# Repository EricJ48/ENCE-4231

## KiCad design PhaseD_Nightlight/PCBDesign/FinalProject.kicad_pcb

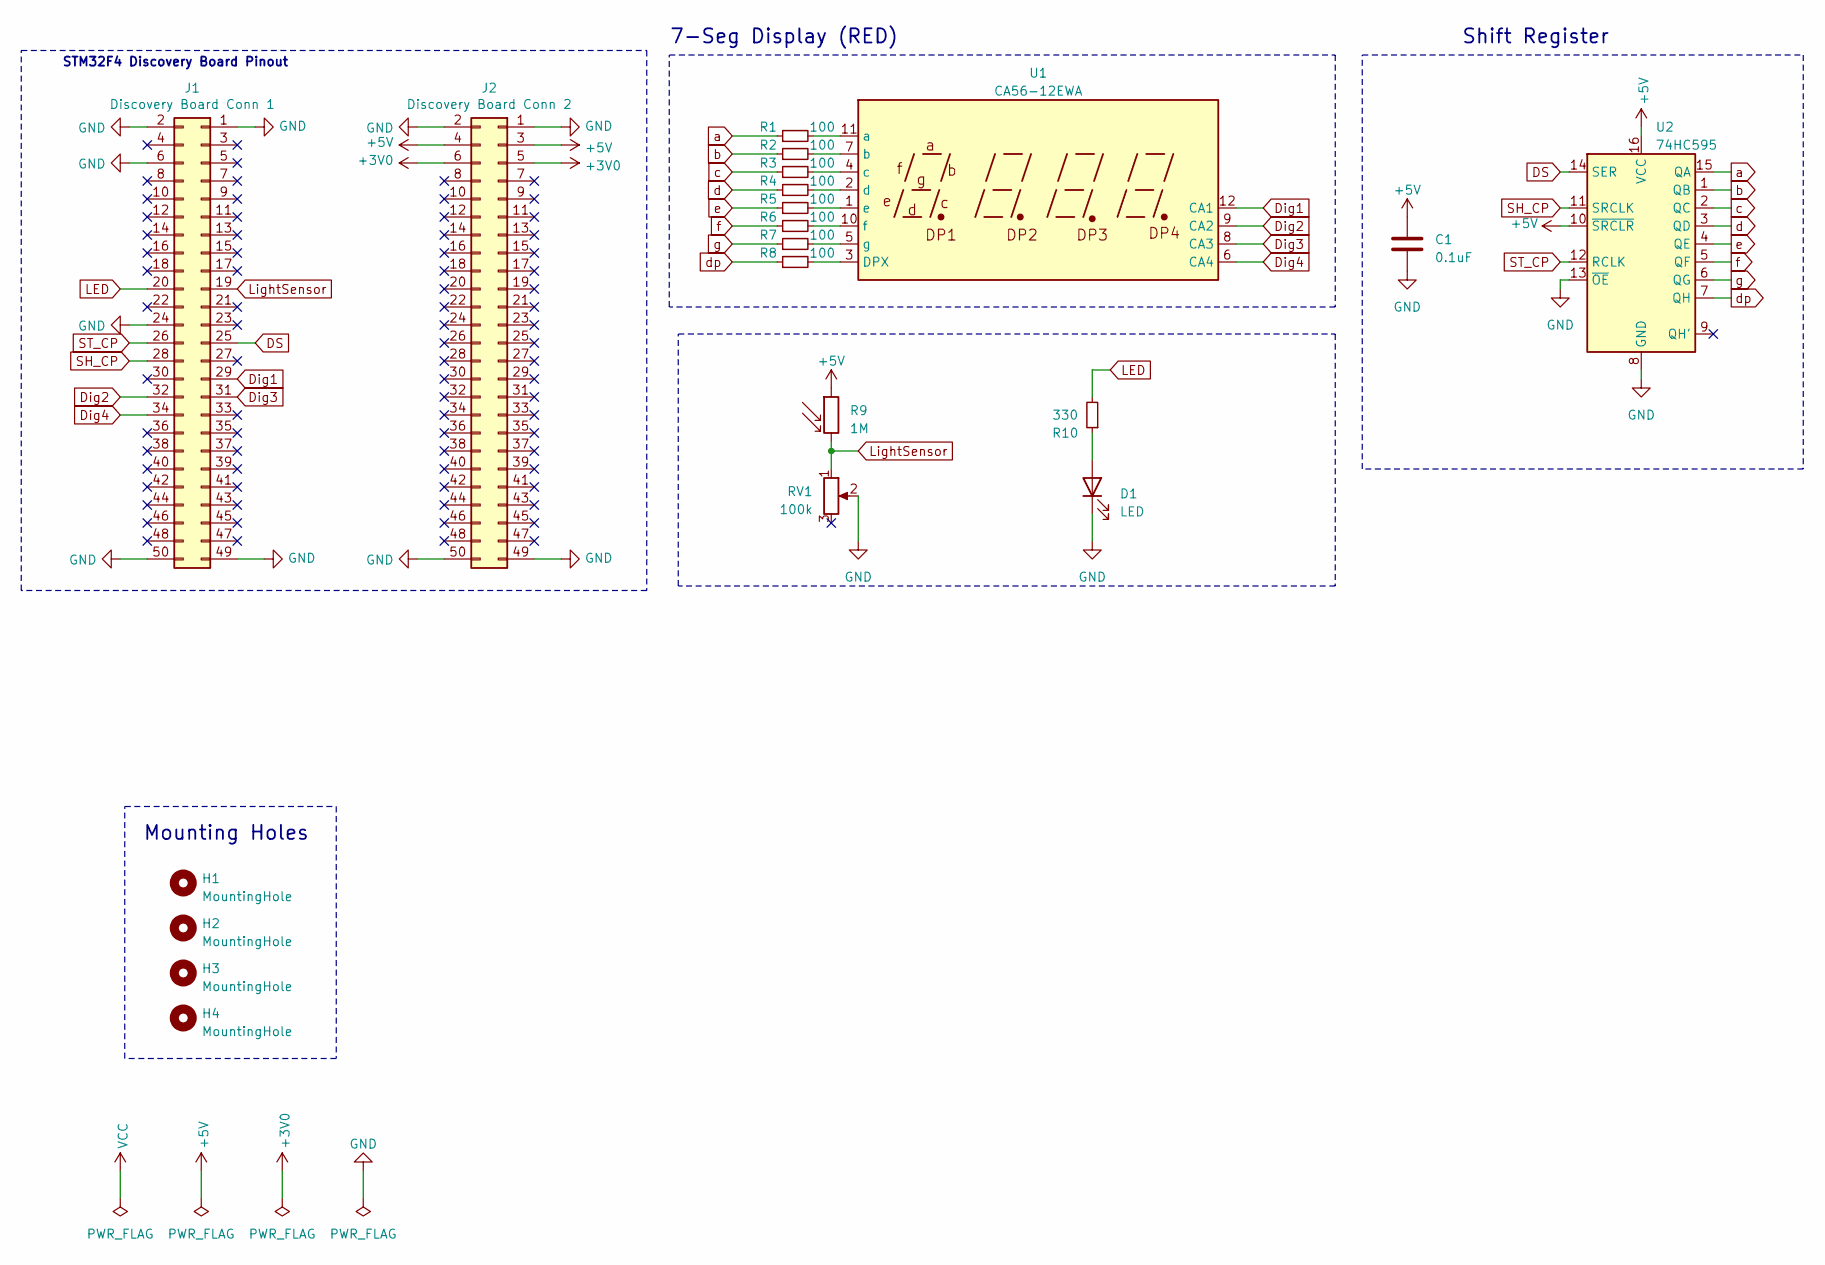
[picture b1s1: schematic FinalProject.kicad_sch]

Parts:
C1: 0.1uF; C_0603_1608Metric
D1: LED; LED_0805_2012Metric
H1, H2, H3, H4: MountingHole; MountingHole_3.2mm_M3_Pad
J1: Discovery Board Conn 1; PinSocket_2x25_P2.54mm_Vertical
J2: Discovery Board Conn 2; PinSocket_2x25_P2.54mm_Vertical
R1, R2, R3, R4, R5, R6, R7, R8: 100; R_0805_2012Metric
R9: 1M; R_Axial_DIN0204_L3.6mm_D1.6mm_P1.90mm_Vertical
R10: 330; R_0805_2012Metric
RV1: 100k; Potentiometer_ACP_CA9-VSMD_Vertical
U1: CA56-12EWA
U2: 74HC595; TSSOP-16_4.4x5mm_P0.65mm

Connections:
+3V0: J2.5, J2.6
+5V: C1.1, J2.3, J2.4, R9.1, U2.10 (~SRCLR), U2.16 (VCC)
DS: J1.25, U2.14 (SER)
Dig1: J1.29, U1.12 (CA1)
Dig2: J1.32, U1.9 (CA2)
Dig3: J1.31, U1.8 (CA3)
Dig4: J1.34, U1.6 (CA4)
GND: C1.2, D1.1 (K), J1.1, J1.2, J1.6, J1.24, J1.49, J1.50, J2.1, J2.2, J2.49, J2.50, RV1.2, U2.8 (GND), U2.13 (~OE)
LED: J1.20, R10.2
LightSensor: J1.19, R9.2, RV1.1
unnamed: D1.2 (A), R10.1
unnamed: R8.2, U1.3 (DPX)
unnamed: R1.2, U1.11 (a)
unnamed: R2.2, U1.7 (b)
unnamed: R3.2, U1.4 (c)
unnamed: R4.2, U1.2 (d)
unnamed: R5.2, U1.1 (e)
unnamed: R6.2, U1.10 (f)
unnamed: R7.2, U1.5 (g)
SH_CP: J1.28, U2.11 (SRCLK)
ST_CP: J1.26, U2.12 (RCLK)
a: R1.1, U2.15 (QA)
b: R2.1, U2.1 (QB)
c: R3.1, U2.2 (QC)
d: R4.1, U2.3 (QD)
dp: R8.1, U2.7 (QH)
e: R5.1, U2.4 (QE)
f: R6.1, U2.5 (QF)
g: R7.1, U2.6 (QG)

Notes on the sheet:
Mounting Holes
STM32F4 Discovery Board Pinout
7-Seg Display (RED)
Shift Register

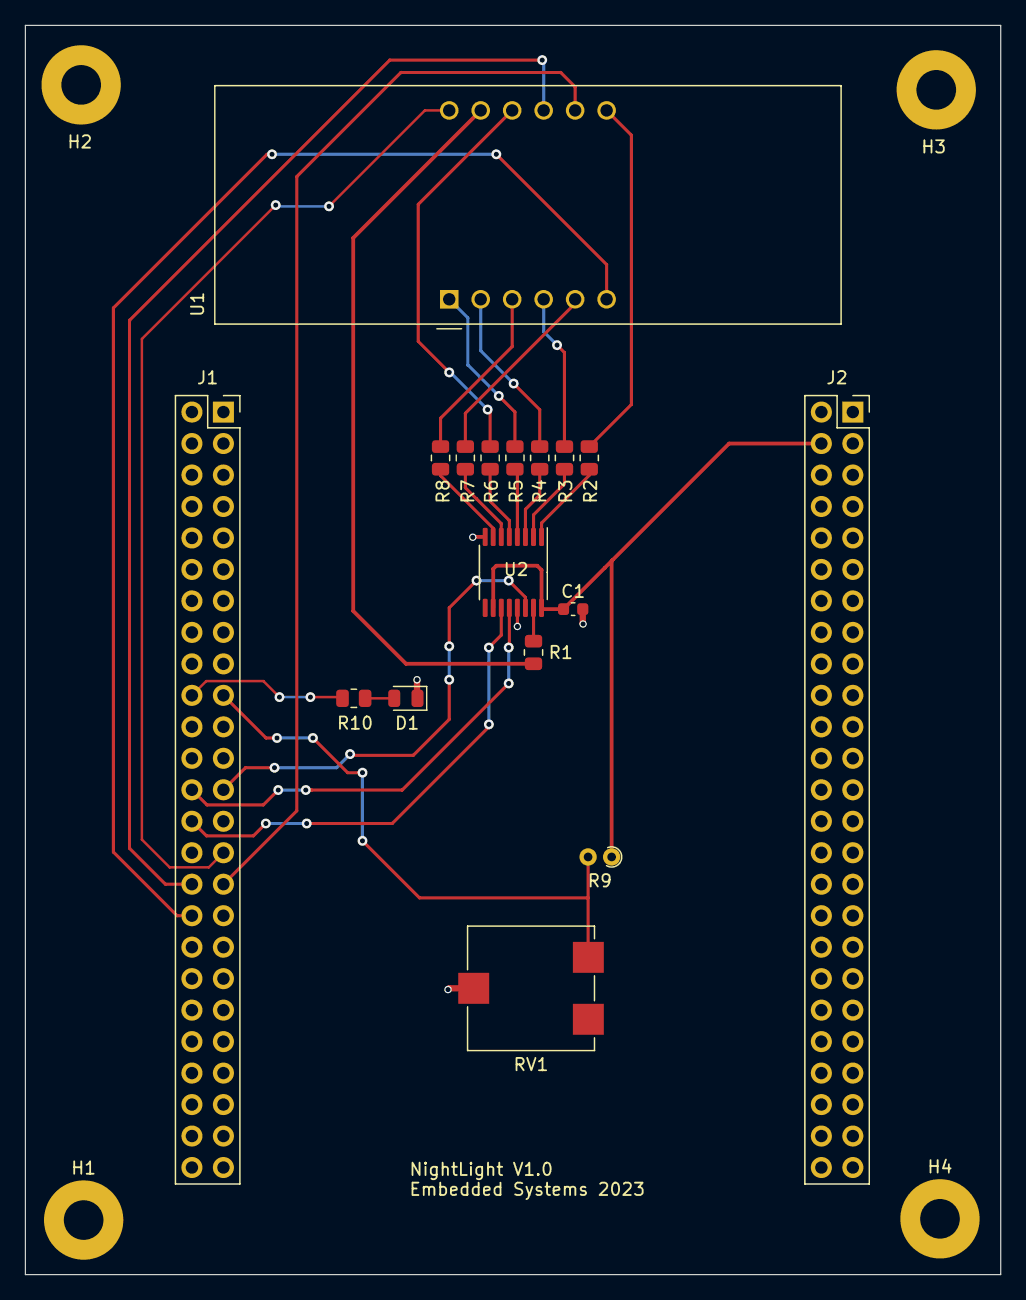
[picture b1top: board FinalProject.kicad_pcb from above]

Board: 2 copper layers, 78.7 x 100.8 mm, 21 parts (0 on the bottom side), 29 nets.

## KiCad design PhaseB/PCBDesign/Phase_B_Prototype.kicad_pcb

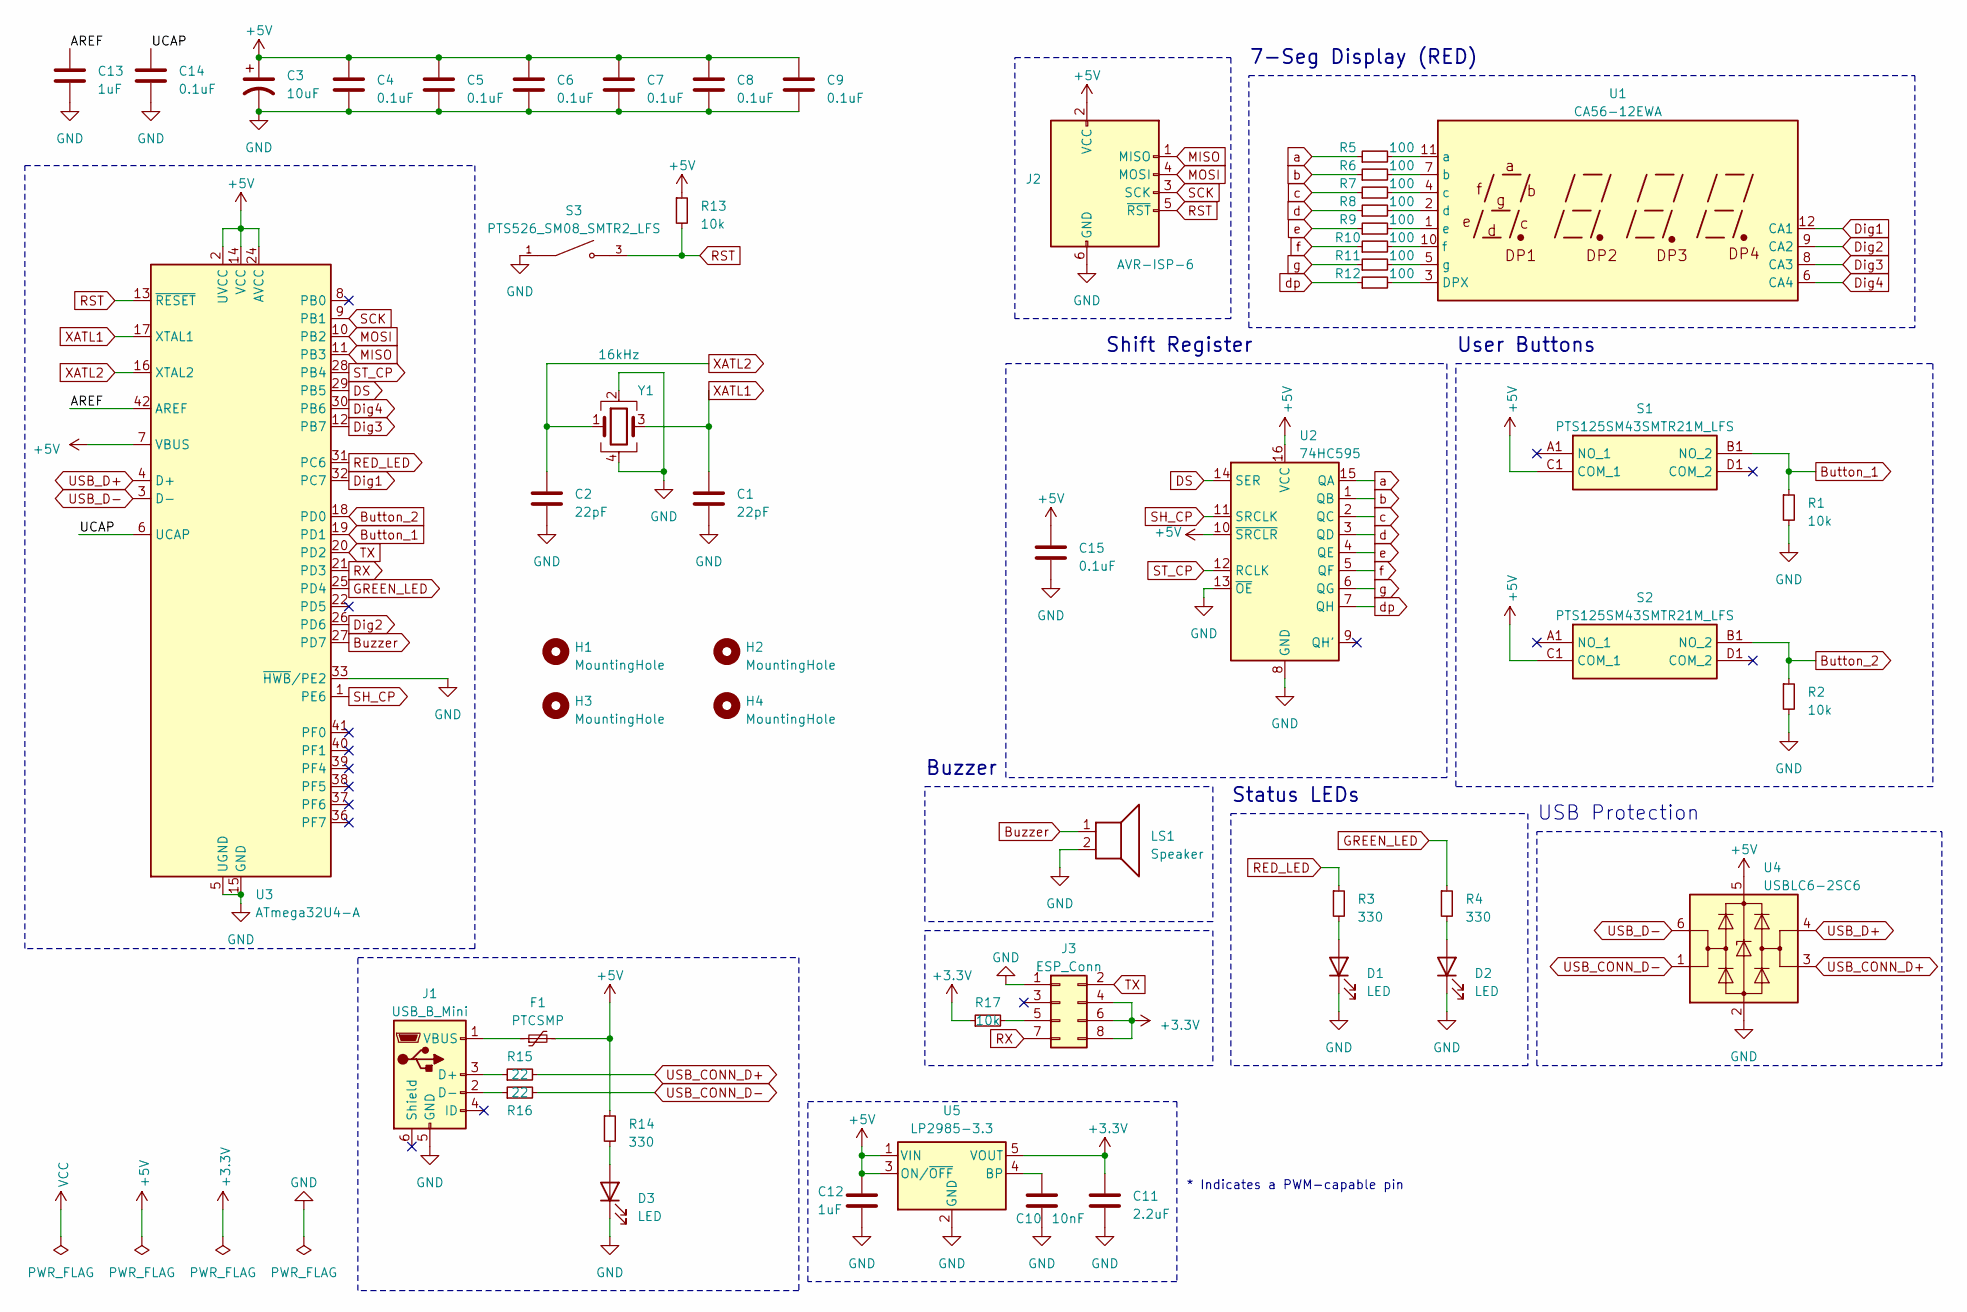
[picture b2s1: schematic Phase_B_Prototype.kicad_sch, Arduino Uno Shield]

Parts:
C1, C2: 22pF; C_0603_1608Metric
C3: 10uF; C_0805_2012Metric
C4, C5, C6, C7, C8, C9, C14, C15: 0.1uF; C_0603_1608Metric
C10: 10nF; C_0603_1608Metric
C11: 2.2uF; C_0603_1608Metric
C12, C13: 1uF; C_0603_1608Metric
D1, D2, D3: LED; LED_0805_2012Metric
F1: PTCSMP; Fuse_1812_4532Metric
H1, H2, H3, H4: MountingHole; MountingHole_3mm
J1: USB_B_Mini; USB_Mini-B_Lumberg_2486_01_Horizontal
J2: AVR-ISP-6; PinHeader_2x03_P2.54mm_Vertical
J3: ESP_Conn; PinSocket_2x04_P2.54mm_Vertical
LS1: Speaker; Buzzer_12x9.5RM7.6
R1, R2, R13, R17: 10k; R_0603_1608Metric
R3, R4, R14: 330; R_0805_2012Metric
R5, R6, R7, R8, R9, R10, R11, R12: 100; R_0805_2012Metric
R15, R16: 22; R_0603_1608Metric
S1, S2: PTS125SM43SMTR21M_LFS; PTS125_SMD_Button; Manufacturer_Part_Number PTS125SM43SMTR21M LFS; Mouser Part Number 611-PTS125S43SMTRLFS
S3: PTS526_SM08_SMTR2_LFS; PTS526_SMD_Button; PARTREV 20 mar 19
U1: CA56-12EWA
U2: 74HC595; TSSOP-16_4.4x5mm_P0.65mm
U3: ATmega32U4-A; TQFP-44_10x10mm_P0.8mm
U4: USBLC6-2SC6; SOT-23-6
U5: LP2985-3.3; SOT-23-5
Y1: 16kHz; Crystal_SMD_Abracon_ABM8G-4Pin_3.2x2.5mm

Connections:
+3.3V: C11.1, J3.4, J3.6, J3.8, R17.1, U5.5 (VOUT)
+5V: C3.1, C4.1, C5.1, C6.1, C7.1, C8.1, C9.1, C12.1, C15.1, F1.2, J2.2 (VCC), R13.1, R14.1, S1.C1 (COM_1), S2.C1 (COM_1), U2.10 (~SRCLR), U2.16 (VCC), U3.2 (UVCC), U3.7 (VBUS), U3.14 (VCC), U3.24 (AVCC), U3.34 (VCC), U3.44 (AVCC), U4.5 (VBUS), U5.1 (VIN), U5.3 (ON/~OFF)
/AREF: C13.1, U3.42 (AREF)
/UCAP: C14.1, U3.6 (UCAP)
Button_1: R1.1, S1.B1 (NO_2), U3.19 (PD1)
Button_2: R2.1, S2.B1 (NO_2), U3.18 (PD0)
Buzzer: LS1.1, U3.27 (PD7)
DS: U2.14 (SER), U3.29 (PB5)
Dig1: U1.12 (CA1), U3.32 (PC7)
Dig2: U1.9 (CA2), U3.26 (PD6)
Dig3: U1.8 (CA3), U3.12 (PB7)
Dig4: U1.6 (CA4), U3.30 (PB6)
GND: C1.2, C2.2, C3.2, C4.2, C5.2, C6.2, C7.2, C8.2, C9.2, C10.2, C11.2, C12.2, C13.2, C14.2, C15.2, D1.1 (K), D2.1 (K), D3.1 (K), J1.5 (GND), J2.6 (GND), J3.1, LS1.2, R1.2, R2.2, S3.1, U2.8 (GND), U2.13 (~OE), U3.5 (UGND), U3.15 (GND), U3.23 (GND), U3.33 (~HWB/PE2), U3.35 (GND), U3.43 (GND), U4.2 (GND), U5.2 (GND), Y1.2, Y1.4
GREEN_LED: R4.1, U3.25 (PD4)
MISO: J2.1 (MISO), U3.11 (PB3)
MOSI: J2.4 (MOSI), U3.10 (PB2)
unnamed: D1.2 (A), R3.2
unnamed: D2.2 (A), R4.2
unnamed: D3.2 (A), R14.2
unnamed: J1.3 (D+), R15.1
unnamed: J1.2 (D-), R16.1
unnamed: F1.1, J1.1 (VBUS)
unnamed: J3.5, R17.2
unnamed: R12.2, U1.3 (DPX)
unnamed: R5.2, U1.11 (a)
unnamed: R6.2, U1.7 (b)
unnamed: R7.2, U1.4 (c)
unnamed: R8.2, U1.2 (d)
unnamed: R9.2, U1.1 (e)
unnamed: R10.2, U1.10 (f)
unnamed: R11.2, U1.5 (g)
unnamed: C10.1, U5.4 (BP)
RED_LED: R3.1, U3.31 (PC6)
RST: J2.5 (~RST), R13.2, S3.3, U3.13 (~RESET)
RX: J3.7, U3.21 (PD3)
SCK: J2.3 (SCK), U3.9 (PB1)
SH_CP: U2.11 (SRCLK), U3.1 (PE6)
ST_CP: U2.12 (RCLK), U3.28 (PB4)
TX: J3.2, U3.20 (PD2)
USB_CONN_D+: R15.2, U4.3 (I/O2)
USB_CONN_D-: R16.2, U4.1 (I/O1)
USB_D+: U3.4 (D+), U4.4 (I/O2)
USB_D-: U3.3 (D-), U4.6 (I/O1)
XATL1: C1.1, U3.17 (XTAL1), Y1.3
XATL2: C2.1, U3.16 (XTAL2), Y1.1
a: R5.1, U2.15 (QA)
b: R6.1, U2.1 (QB)
c: R7.1, U2.2 (QC)
d: R8.1, U2.3 (QD)
dp: R12.1, U2.7 (QH)
e: R9.1, U2.4 (QE)
f: R10.1, U2.5 (QF)
g: R11.1, U2.6 (QG)

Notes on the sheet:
Shift Register
Status LEDs
User Buttons
Buzzer
* Indicates a PWM-capable pin
USB Protection
7-Seg Display (RED)

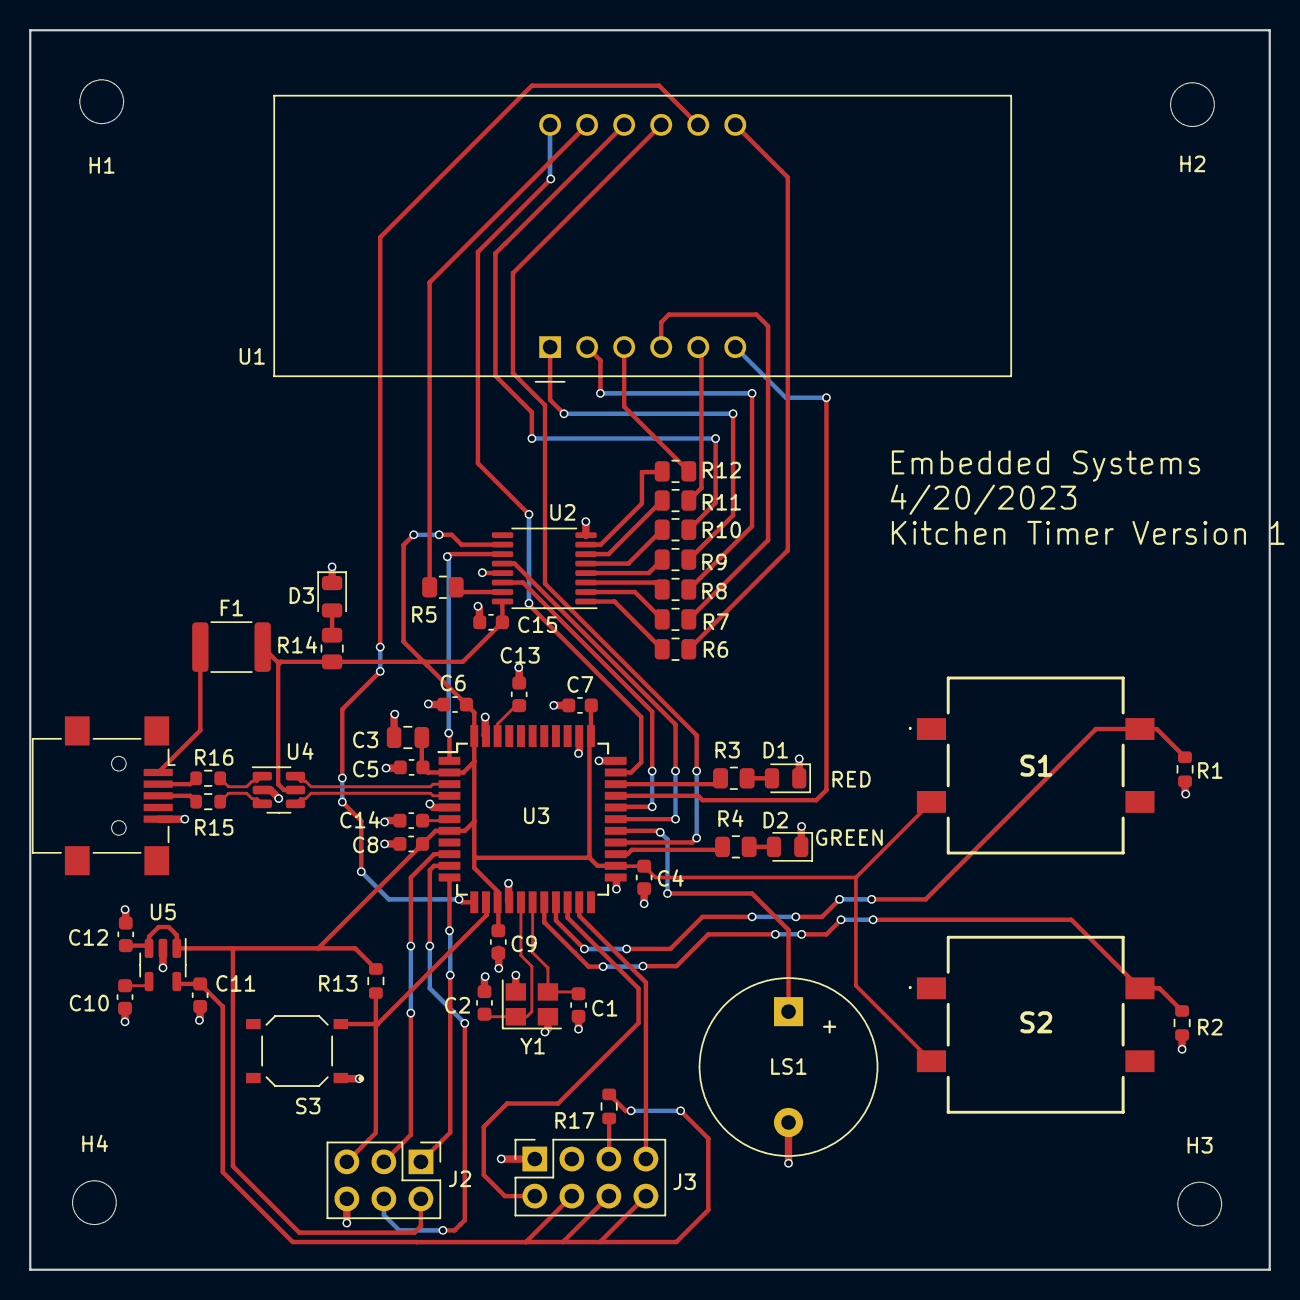
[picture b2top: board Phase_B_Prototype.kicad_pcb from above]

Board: 2 copper layers, 85.0 x 85.0 mm, 53 parts (0 on the bottom side), 53 nets.

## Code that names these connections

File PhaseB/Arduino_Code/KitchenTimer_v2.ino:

#define BUTTON_2  2  // Inc Timer
#define BUTTON_1  3  // Start/Stop Timer and Stop Buzzer
#define GREEN_LED 4
#define RED_LED   5
#define BUZZER    6

#define DATA      9 // DS
#define LATCH     8 // ST_CP
#define CLOCK     7 // SH_CP

#define DIGIT_4   10
#define DIGIT_3   11
#define DIGIT_2   12
#define DIGIT_1   13

// 7-Seg Display Variables
unsigned char gtable[]=
{0x3f,0x06,0x5b,0x4f,0x66,0x6d,0x7d,0x07,0x7f,0x6f,0x77,0x7c
,0x39,0x5e,0x79,0x71,0x00};
byte gCurrentDigit;

// Volatile Variables
volatile unsigned char gISRFlag1   = 0;
volatile unsigned char gBuzzerFlag = 0;

// Timer Variables
#define DEFAULT_COUNT 30     // default value is 30secs
volatile int  gCount        = DEFAULT_COUNT;
unsigned char gTimerRunning = 0; 

unsigned int gReloadTimer1 = 62500; // corresponds to 1 second
byte         gReloadTimer2 = 10;  // display refresh time

/**
 * @brief Setup peripherals and timers
 * @param
 * @return
 */
void setup() {
  // LEDs Pins
  pinMode(RED_LED, OUTPUT);
  pinMode(GREEN_LED, OUTPUT);

  // LEDs -> Timer Stopped
  digitalWrite(RED_LED, HIGH);
  digitalWrite(GREEN_LED, HIGH);

  // Button Pins
  pinMode(BUTTON_1, INPUT_PULLUP);
  attachInterrupt(digitalPinToInterrupt(BUTTON_1), buttonISR1, RISING);
  pinMode(BUTTON_2, INPUT_PULLUP);
  attachInterrupt(digitalPinToInterrupt(BUTTON_2), buttonISR2, RISING);

  // Buzer Pins
  pinMode(BUZZER, OUTPUT);

  // Buzzer -> Off
  digitalWrite(BUZZER,LOW);

  // 7-Seg Display
  pinMode(DIGIT_1, OUTPUT);
  pinMode(DIGIT_2, OUTPUT);
  pinMode(DIGIT_3, OUTPUT);
  pinMode(DIGIT_4, OUTPUT);

  // Shift Register Pins
  pinMode(LATCH, OUTPUT);
  pinMode(CLOCK, OUTPUT);
  pinMode(DATA, OUTPUT);

  dispOff();  // turn off the display

  // Initialize Timer1 (16bit) -> Used for clock
  // Speed of Timer1 = 16MHz/256 = 62.5 KHz
  noInterrupts();
  TCCR1A = 0;
  TCCR1B = 0;
  OCR1A = gReloadTimer1; // compare match register 16MHz/256
  TCCR1B |= (1<<WGM12);   // CTC mode
  // Start Timer by setting the prescaler -> done using the start button
  //TCCR1B |= (1<<CS12);    // 256 prescaler 
  TIMSK1 |= (1<<OCIE1A);  // enable timer compare interrupt
  interrupts();

  // Initialize Timer2 (8bit) -> Used to refresh display
  // Speed of Timer2 = 16MHz/1024 = 15.625 KHz
  TCCR2A = 0;
  TCCR2B = 0;
  OCR2A = gReloadTimer2;                     // max value 2^8 - 1 = 255
  TCCR2A |= (1<<WGM21);
  TCCR2B = (1<<CS22) | (1<<CS21) | (1<<CS20); // 1204 prescaler
  TIMSK2 |= (1<<OCIE2A);
  interrupts();                               // enable all interrupts
}

/**
 * @brief Shifts the bits through the shift register
 * @param num
 * @param dp
 * @return
 */
void display(unsigned char num, unsigned char dp)
{
  digitalWrite(LATCH, LOW);
  shiftOut(DATA, CLOCK, MSBFIRST, gtable[num] | (dp<<7));
  digitalWrite(LATCH, HIGH);
}

/**
 * @brief Turns the 7-seg display off
 * @param
 * @return
 */
void dispOff()
{
   digitalWrite(DIGIT_1, HIGH);
   digitalWrite(DIGIT_2, HIGH);
   digitalWrite(DIGIT_3, HIGH);
   digitalWrite(DIGIT_4, HIGH);
}

/**
 * @brief Button 2 ISR
 * @param
 * @return
 */
void buttonISR2()
{
  // Increment Clock
  gCount++;
}

/**
 * @brief Button 1 ISR
 * @param
 * @return
 */
void buttonISR1()
{ 
  // Set ISR Flag
  gISRFlag1 = 1;
}

/**
 * @brief Timer 2 ISR
 * @param TIMER2_COMPA_vect
 * @return
 */
ISR(TIMER2_COMPA_vect)   // Timer2 interrupt service routine (ISR)
{
  dispOff();  // turn off the display
 
  switch (gCurrentDigit)
  {
    case 1: //0x:xx
      display( int((gCount/60) / 10) % 6, 0 );   // prepare to display digit 1 (most left)
      digitalWrite(DIGIT_1, LOW);  // turn on digit 1
      break;
 
    case 2: //x0:xx
      display( int(gCount / 60) % 10, 1 );   // prepare to display digit 2
      digitalWrite(DIGIT_2, LOW);     // turn on digit 2
      break;
 
    case 3: //xx:0x
      display( (gCount / 10) % 6, 0 );   // prepare to display digit 3
      digitalWrite(DIGIT_3, LOW);    // turn on digit 3
      break;
 
    case 4: //xx:x0
      display(gCount % 10, 0); // prepare to display digit 4 (most right)
      digitalWrite(DIGIT_4, LOW);  // turn on digit 4
      break;

    default:
      break;
  }
 
  gCurrentDigit = (gCurrentDigit % 4) + 1;
}

/**
 * @brief Timer 1 ISR
 * @param TIMER1_COMPA_vect
 * @return
 */
ISR(TIMER1_COMPA_vect)  // Timer1 interrupt service routine (ISR)
{
  gCount--;

  if(gCount == 0)
  {
      // Stop Timer
      stopTimer1();
      
      // Raise Alarm
      gBuzzerFlag = 1;
      gTimerRunning = 0;
  }
}

/**
 * @brief Stop Timer 1
 * @param
 * @return
 */
void stopTimer1()
{
  // Stop Timer
  TCCR1B &= 0b11111000; // stop clock
  TIMSK1 = 0; // cancel clock timer interrupt
}

/**
 * @brief Start Timer 1
 * @param
 * @return
 */
void startTimer1()
{
  // Start Timer
  TCCR1B |= (1<<CS12);    // 256 prescaler 
  TIMSK1 |= (1<<OCIE1A);  // enable timer compare interrupt
}

/**
 * @brief Turn On Buzzer
 * @param
 * @return
 */
void activeBuzzer()
{
  unsigned char i;
  unsigned char sleepTime = 1; // ms
  
  for(i=0;i<100;i++)
  {
    digitalWrite(BUZZER,HIGH);
    delay(sleepTime);//wait for 1ms
    digitalWrite(BUZZER,LOW);
    delay(sleepTime);//wait for 1ms
  }
}

/**
 * @brief Main Loop
 * @param
 * @return
 */
void loop() 
{
  // Attend Button 2 ISR
  if(gISRFlag1 == 1)
  {
    // Reset ISR Flag
    gISRFlag1 = 0;

    if(gTimerRunning == 0)
    {
      // Start Timer
      gTimerRunning = 1;

      if(gCount == 0)
        gCount = DEFAULT_COUNT;

      if(gBuzzerFlag == 1)
      {
        gBuzzerFlag = 0;

        // LEDs -> Timer Stopped
        digitalWrite(RED_LED, HIGH);
        digitalWrite(GREEN_LED, HIGH);
      }
      else
      {
        startTimer1();
        // LEDs -> Timer Running
        digitalWrite(RED_LED, LOW);
        digitalWrite(GREEN_LED, HIGH);
      }
    }
    else
    {
      // Stop Timer
      stopTimer1();
      gTimerRunning = 0;

      // LEDs -> Timer Running
      digitalWrite(RED_LED, HIGH);
      digitalWrite(GREEN_LED, HIGH);
    }
  }

  // Attend gBuzzerFlag
  if(gBuzzerFlag == 1)
  {
    // Make Noise...
    digitalWrite(RED_LED, HIGH);
    digitalWrite(GREEN_LED, LOW);
    activeBuzzer();
  }
}

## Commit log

2023-04-20 Create Phase B
2023-04-20 Create placeholder
2023-06-01 Create BOM
